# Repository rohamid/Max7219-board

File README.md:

# Max7219-board
MAX7219 breakout board with vertical and horizontal two 7-segment arrangement

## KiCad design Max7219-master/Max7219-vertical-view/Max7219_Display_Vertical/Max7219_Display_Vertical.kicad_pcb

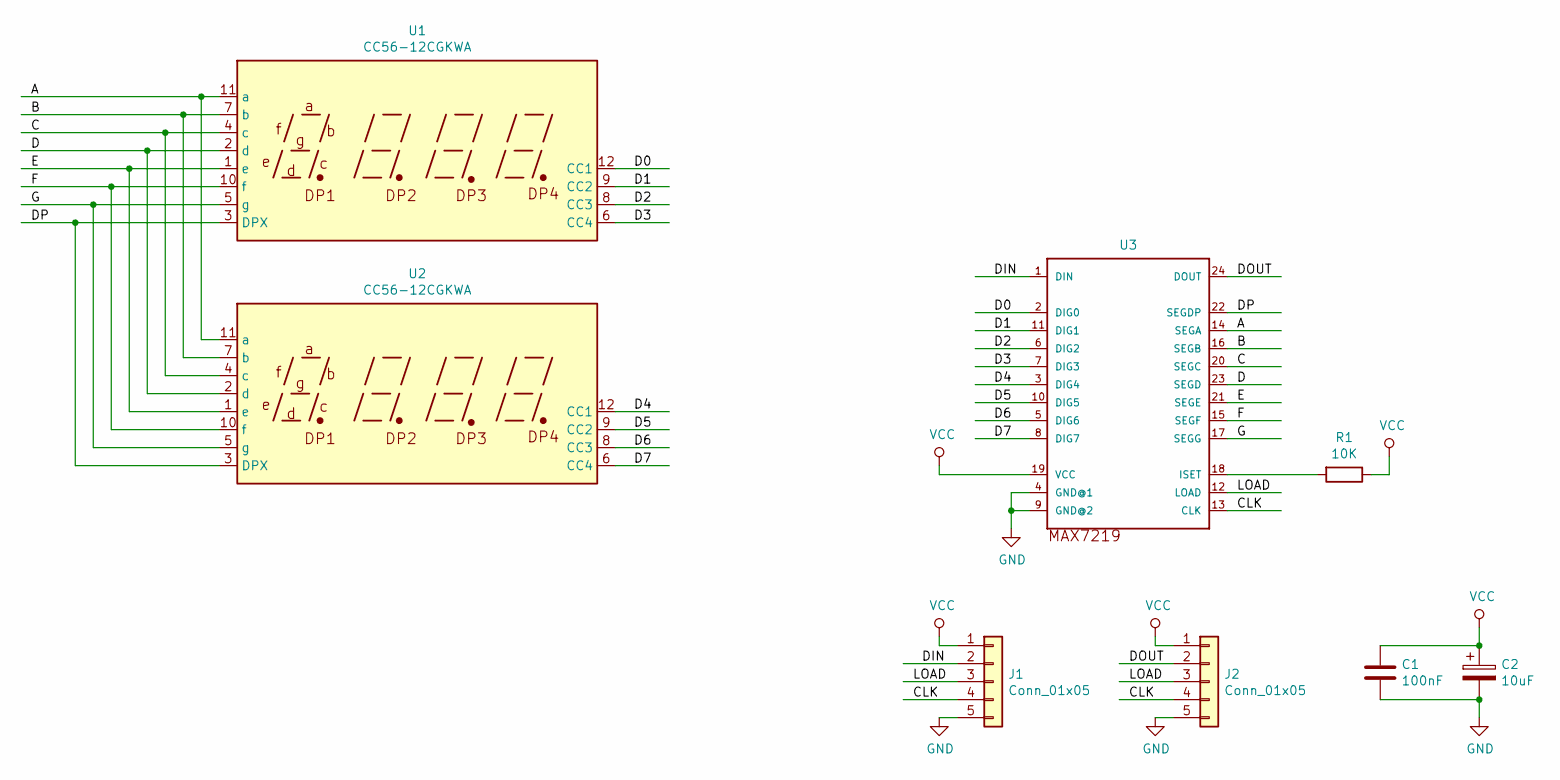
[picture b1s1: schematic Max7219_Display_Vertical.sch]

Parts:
C1: 100nF; C_0805_2012Metric_Pad1.15x1.40mm_HandSolder
C2: 10uF; CP_EIA-3528-12_Kemet-T_Pad1.50x2.35mm_HandSolder
J1, J2: Conn_01x05; PinHeader_1x05_P2.54mm_Vertical
R1: 10K; R_0805_2012Metric_Pad1.15x1.40mm_HandSolder
U1, U2: CC56-12CGKWA; CA56-12CGKWA
U3: MAX7219; SOIC24

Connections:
/A: U1.11 (a), U2.11 (a), U3.14 (SEGA)
/B: U1.7 (b), U2.7 (b), U3.16 (SEGB)
/C: U1.4 (c), U2.4 (c), U3.20 (SEGC)
/CLK: J1.4, J2.4, U3.13 (CLK)
/D: U1.2 (d), U2.2 (d), U3.23 (SEGD)
/D0: U1.12 (CC1), U3.2 (DIG0)
/D1: U1.9 (CC2), U3.11 (DIG1)
/D2: U1.8 (CC3), U3.6 (DIG2)
/D3: U1.6 (CC4), U3.7 (DIG3)
/D4: U2.12 (CC1), U3.3 (DIG4)
/D5: U2.9 (CC2), U3.10 (DIG5)
/D6: U2.8 (CC3), U3.5 (DIG6)
/D7: U2.6 (CC4), U3.8 (DIG7)
/DIN: J1.2, U3.1 (DIN)
/DOUT: J2.2, U3.24 (DOUT)
/DP: U1.3 (DPX), U2.3 (DPX), U3.22 (SEGDP)
/E: U1.1 (e), U2.1 (e), U3.21 (SEGE)
/F: U1.10 (f), U2.10 (f), U3.15 (SEGF)
/G: U1.5 (g), U2.5 (g), U3.17 (SEGG)
/LOAD: J1.3, J2.3, U3.12 (LOAD)
GND: C1.2, C2.2, J1.5, J2.5, U3.4 (GND@1), U3.9 (GND@2)
unnamed: R1.2, U3.18 (ISET)
VCC: C1.1, C2.1, J1.1, J2.1, R1.1, U3.19 (VCC)

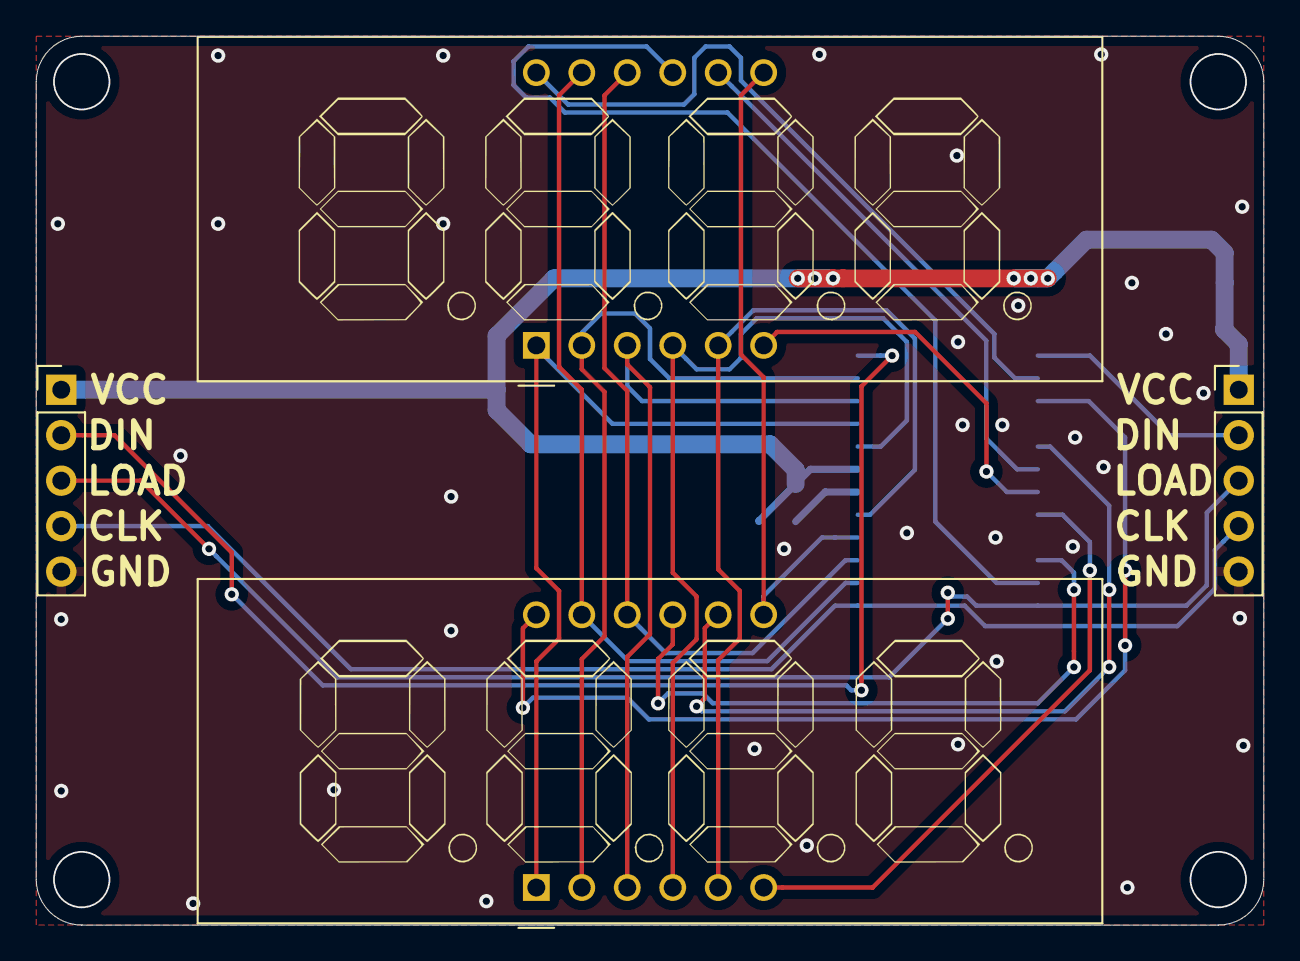
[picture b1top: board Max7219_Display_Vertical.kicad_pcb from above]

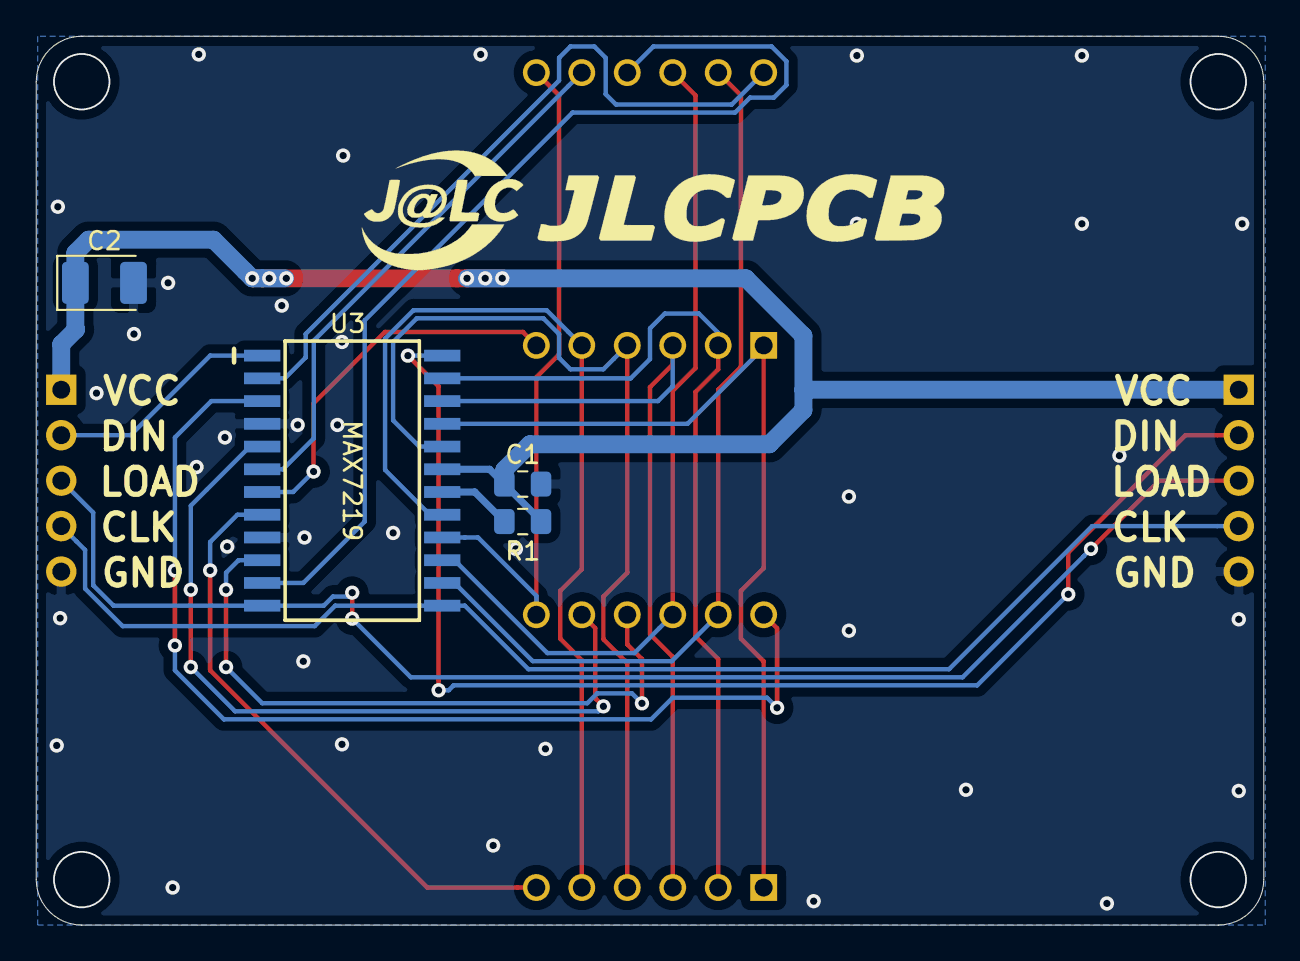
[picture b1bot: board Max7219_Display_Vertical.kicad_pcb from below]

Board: 2 copper layers, 68.6 x 49.7 mm, 8 parts (4 on the bottom side), 23 nets.
